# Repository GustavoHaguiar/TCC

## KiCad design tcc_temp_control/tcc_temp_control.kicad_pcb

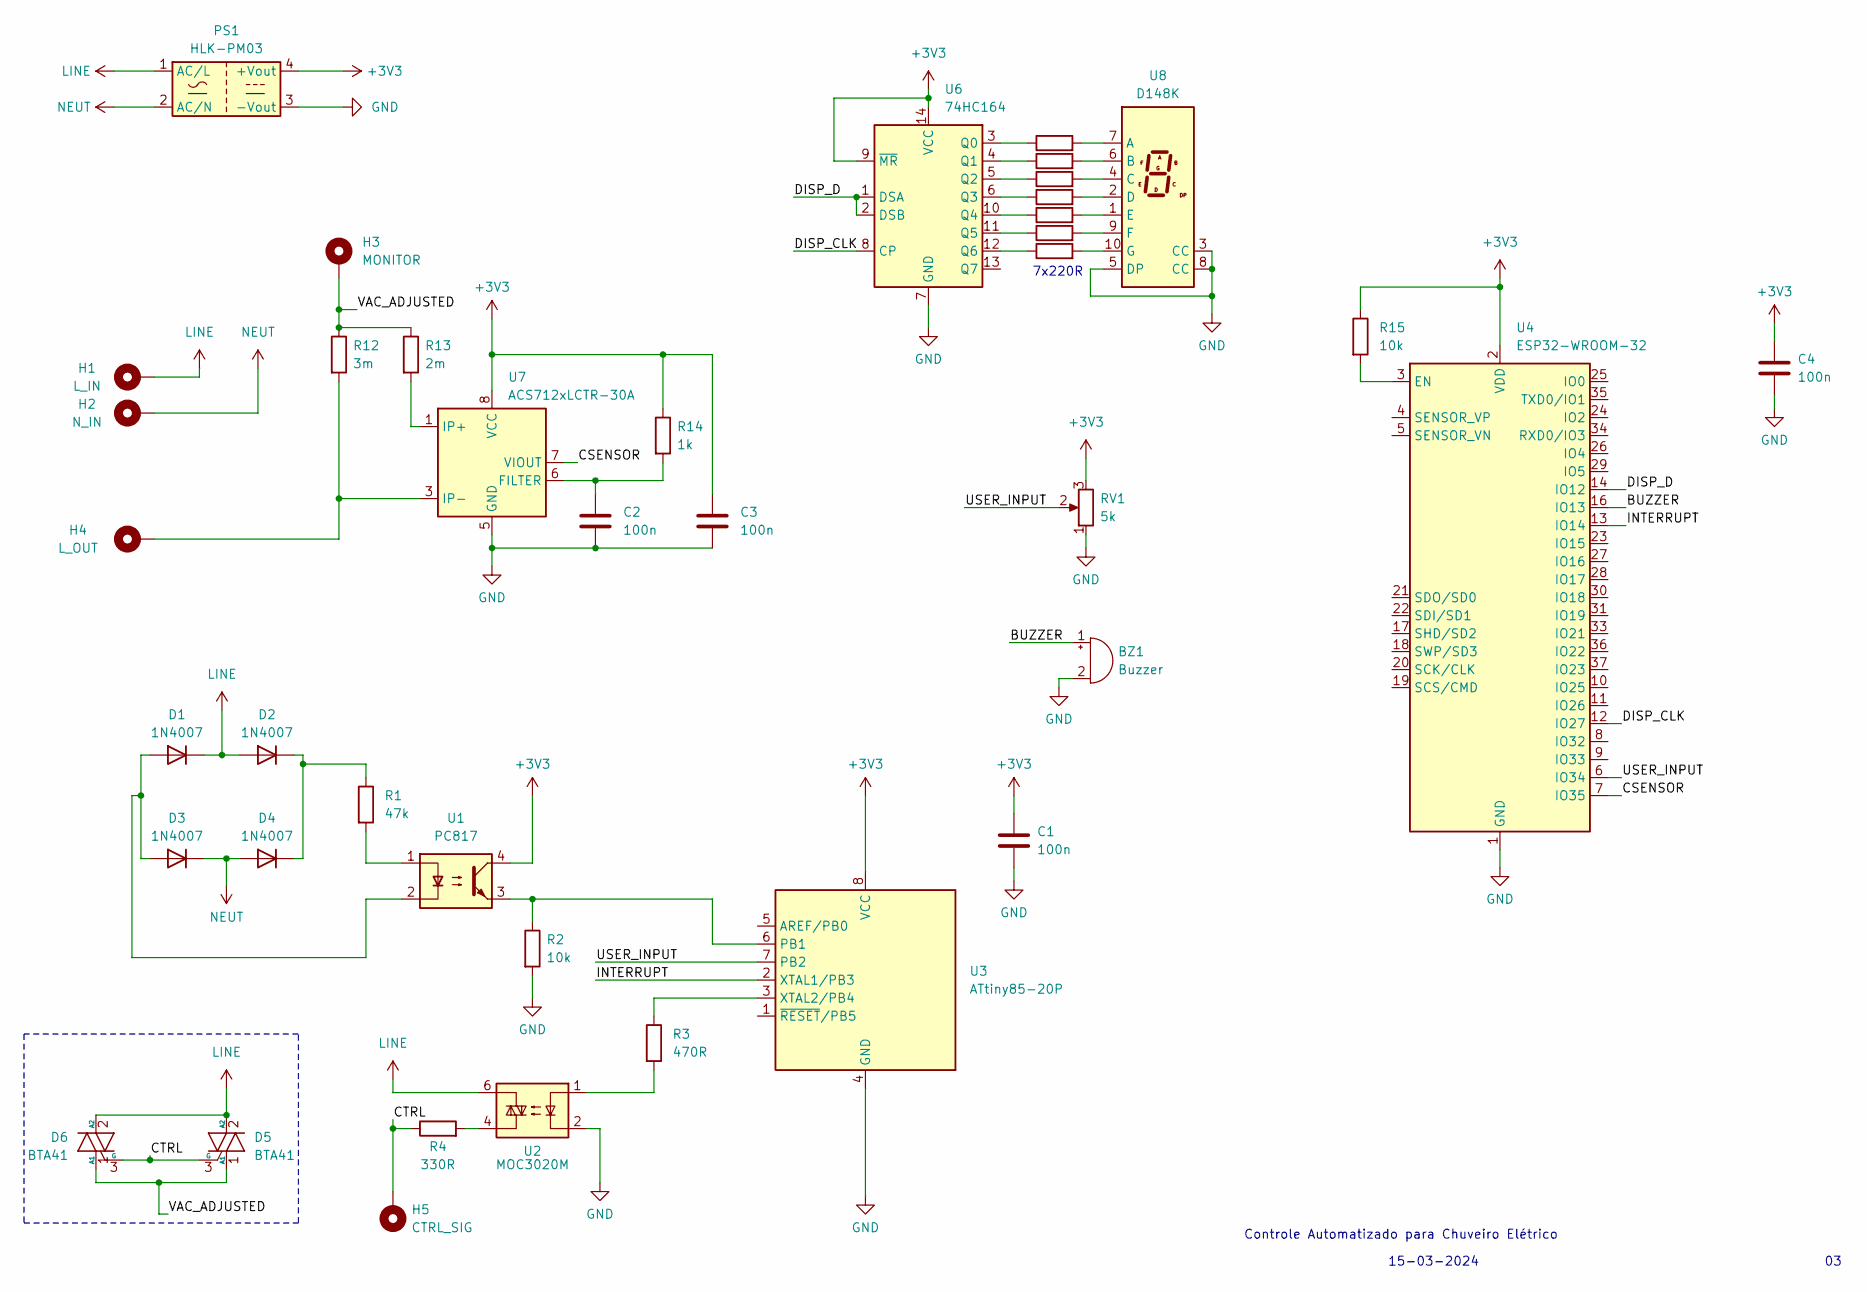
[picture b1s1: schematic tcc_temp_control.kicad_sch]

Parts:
BZ1: Buzzer; Buzzer_12x9.5RM7.6
C1, C2, C3, C4: 100n; C_0805_2012Metric_Pad1.18x1.45mm_HandSolder
D1, D2, D3, D4: 1N4007; D_SMA
D5, D6: BTA41; TO-247-3_Vertical
H1: L_IN; MountingHole_6.4mm_M6_DIN965_Pad
H2: N_IN; MountingHole_6.4mm_M6_DIN965_Pad
H3: MONITOR; MountingHole_6.4mm_M6_DIN965_Pad
H4: L_OUT; MountingHole_6.4mm_M6_DIN965_Pad
H5: CTRL_SIG; MountingHole_2.5mm_Pad
PS1: HLK-PM03; Converter_ACDC_HiLink_HLK-PMxx
R1: 47k; R_Axial_DIN0617_L17.0mm_D6.0mm_P20.32mm_Horizontal
R2, R15: 10k; R_0805_2012Metric_Pad1.20x1.40mm_HandSolder
R3: 470R; R_0805_2012Metric_Pad1.20x1.40mm_HandSolder
R4: 330R; R_Axial_DIN0207_L6.3mm_D2.5mm_P10.16mm_Horizontal
R5, R6, R7, R8, R9, R10, R11: 220R; R_0805_2012Metric_Pad1.20x1.40mm_HandSolder
R12: 3m; R_2512_6332Metric_Pad1.40x3.35mm_HandSolder
R13: 2m; R_2512_6332Metric_Pad1.40x3.35mm_HandSolder
R14: 1k; R_0805_2012Metric_Pad1.20x1.40mm_HandSolder
RV1: 5k; Potentiometer_Alps_RK09K_Single_Vertical
U1: PC817; DIP-4_W7.62mm
U2: MOC3020M; DIP-6_W7.62mm
U3: ATtiny85-20P; DIP-8_W7.62mm
U4: ESP32-WROOM-32
U6: 74HC164; SOIC-14_3.9x8.7mm_P1.27mm
U7: ACS712xLCTR-30A; SOIC-8_3.9x4.9mm_P1.27mm
U8: D148K; D1X8K

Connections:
+3V3: C1.1, C3.1, C4.1, PS1.4 (+Vout), R14.1, R15.1, RV1.3, U1.4, U3.8 (VCC), U4.2 (VDD), U6.9 (~MR), U6.14 (VCC), U7.8 (VCC)
/BUZZER: BZ1.1 (-), U4.16 (IO13)
/CSENSOR: U4.7 (IO35), U7.7 (VIOUT)
/CTRL: D5.3 (G), D6.3 (G), H5.1, R4.1
/DISP_CLK: U4.12 (IO27), U6.8 (CP)
/DISP_D: U4.14 (IO12), U6.1 (DSA), U6.2 (DSB)
/INTERRUPT: U3.2 (XTAL1/PB3), U4.13 (IO14)
/USER_INPUT: RV1.2, U3.7 (PB2), U4.6 (IO34)
/VAC_ADJUSTED: D5.1 (A1), D6.1 (A1), H3.1, R12.1, R13.1
GND: BZ1.2 (+), C1.2, C2.2, C3.2, C4.2, PS1.3 (-Vout), R2.2, RV1.1, U2.2, U3.4 (GND), U4.1 (GND), U4.15 (GND), U4.38 (GND), U4.39 (GND), U6.7 (GND), U7.5 (GND), U8.3 (CC), U8.5 (DP), U8.8 (CC)
LINE: D1.1 (K), D2.2 (A), D5.2 (A2), D6.2 (A2), H1.1, PS1.1 (AC/L), U2.6
NEUT: D3.1 (K), D4.2 (A), H2.1, PS1.2 (AC/N)
unnamed: D1.2 (A), D3.2 (A), U1.2
unnamed: D2.1 (K), D4.1 (K), R1.1
unnamed: H4.1, R12.2, U7.3 (IP-), U7.4 (IP-)
unnamed: R1.2, U1.1
unnamed: R3.2, U2.1
unnamed: R4.2, U2.4
unnamed: R13.2, U7.1 (IP+), U7.2 (IP+)
unnamed: R2.1, U1.3, U3.6 (PB1)
unnamed: R3.1, U3.3 (XTAL2/PB4)
unnamed: R15.2, U4.3 (EN)
unnamed: R5.1, U6.3 (Q0)
unnamed: R6.1, U6.4 (Q1)
unnamed: R7.1, U6.5 (Q2)
unnamed: R8.1, U6.6 (Q3)
unnamed: R9.1, U6.10 (Q4)
unnamed: R10.1, U6.11 (Q5)
unnamed: R11.1, U6.12 (Q6)
unnamed: C2.1, R14.2, U7.6 (FILTER)
unnamed: R5.2, U8.7 (A)
unnamed: R6.2, U8.6 (B)
unnamed: R7.2, U8.4 (C)
unnamed: R8.2, U8.2 (D)
unnamed: R9.2, U8.1 (E)
unnamed: R10.2, U8.9 (F)
unnamed: R11.2, U8.10 (G)

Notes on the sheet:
Controle Automatizado para Chuveiro Elétrico
7x220R
15-03-2024

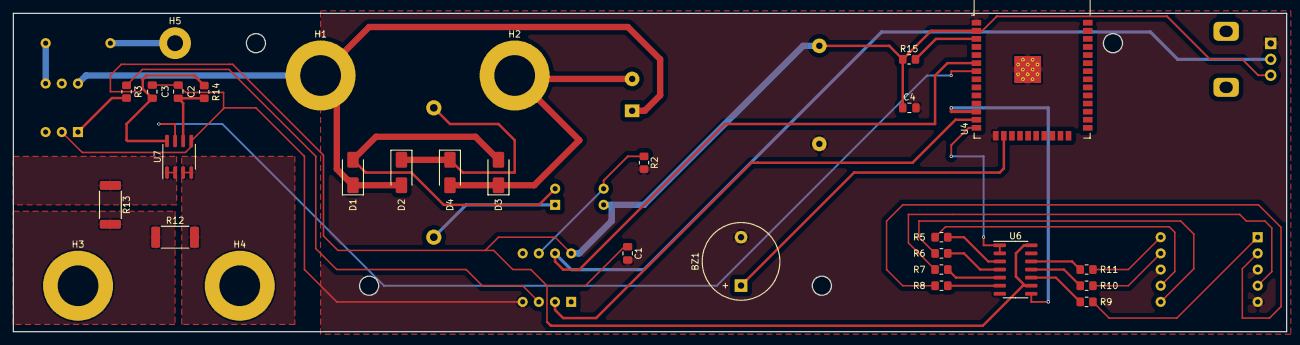
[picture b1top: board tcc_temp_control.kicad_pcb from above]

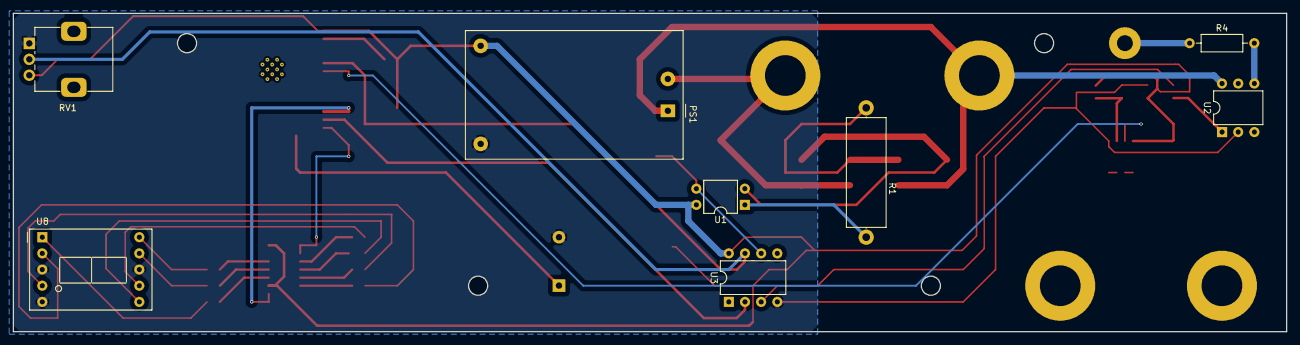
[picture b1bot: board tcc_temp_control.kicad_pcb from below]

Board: 2 copper layers, 200.0 x 50.0 mm, 38 parts (8 on the bottom side), 37 nets.

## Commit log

2024-02-11 Interface finished - version with Arduino Uno
2024-02-15 new version of display control - missed some updates, add server
2024-02-15 feat: update code
2024-02-15 added schematic
2024-02-20 added dual core processing
2024-02-24 finished schematic and update the interface code
2024-03-15 comunicação get e post feita entre o servidor web - Server 2
2024-05-03 Update to save my changes
2024-05-14 adding the original file of TCC
2024-06-19 Added new archive .ino with the original code of tcc project, it's in main folder
2024-07-01 quase tudo pronto
2024-07-23 time of bath is implemented, and postLog development
2024-10-07 v1 finished!
2024-11-18 last version, today I'm presenting my thesis
